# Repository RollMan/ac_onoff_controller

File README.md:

## Appearance

## Improvements
The 2nd servo motor (M2) must be connected to PB2 which is assigned as compare output mode.

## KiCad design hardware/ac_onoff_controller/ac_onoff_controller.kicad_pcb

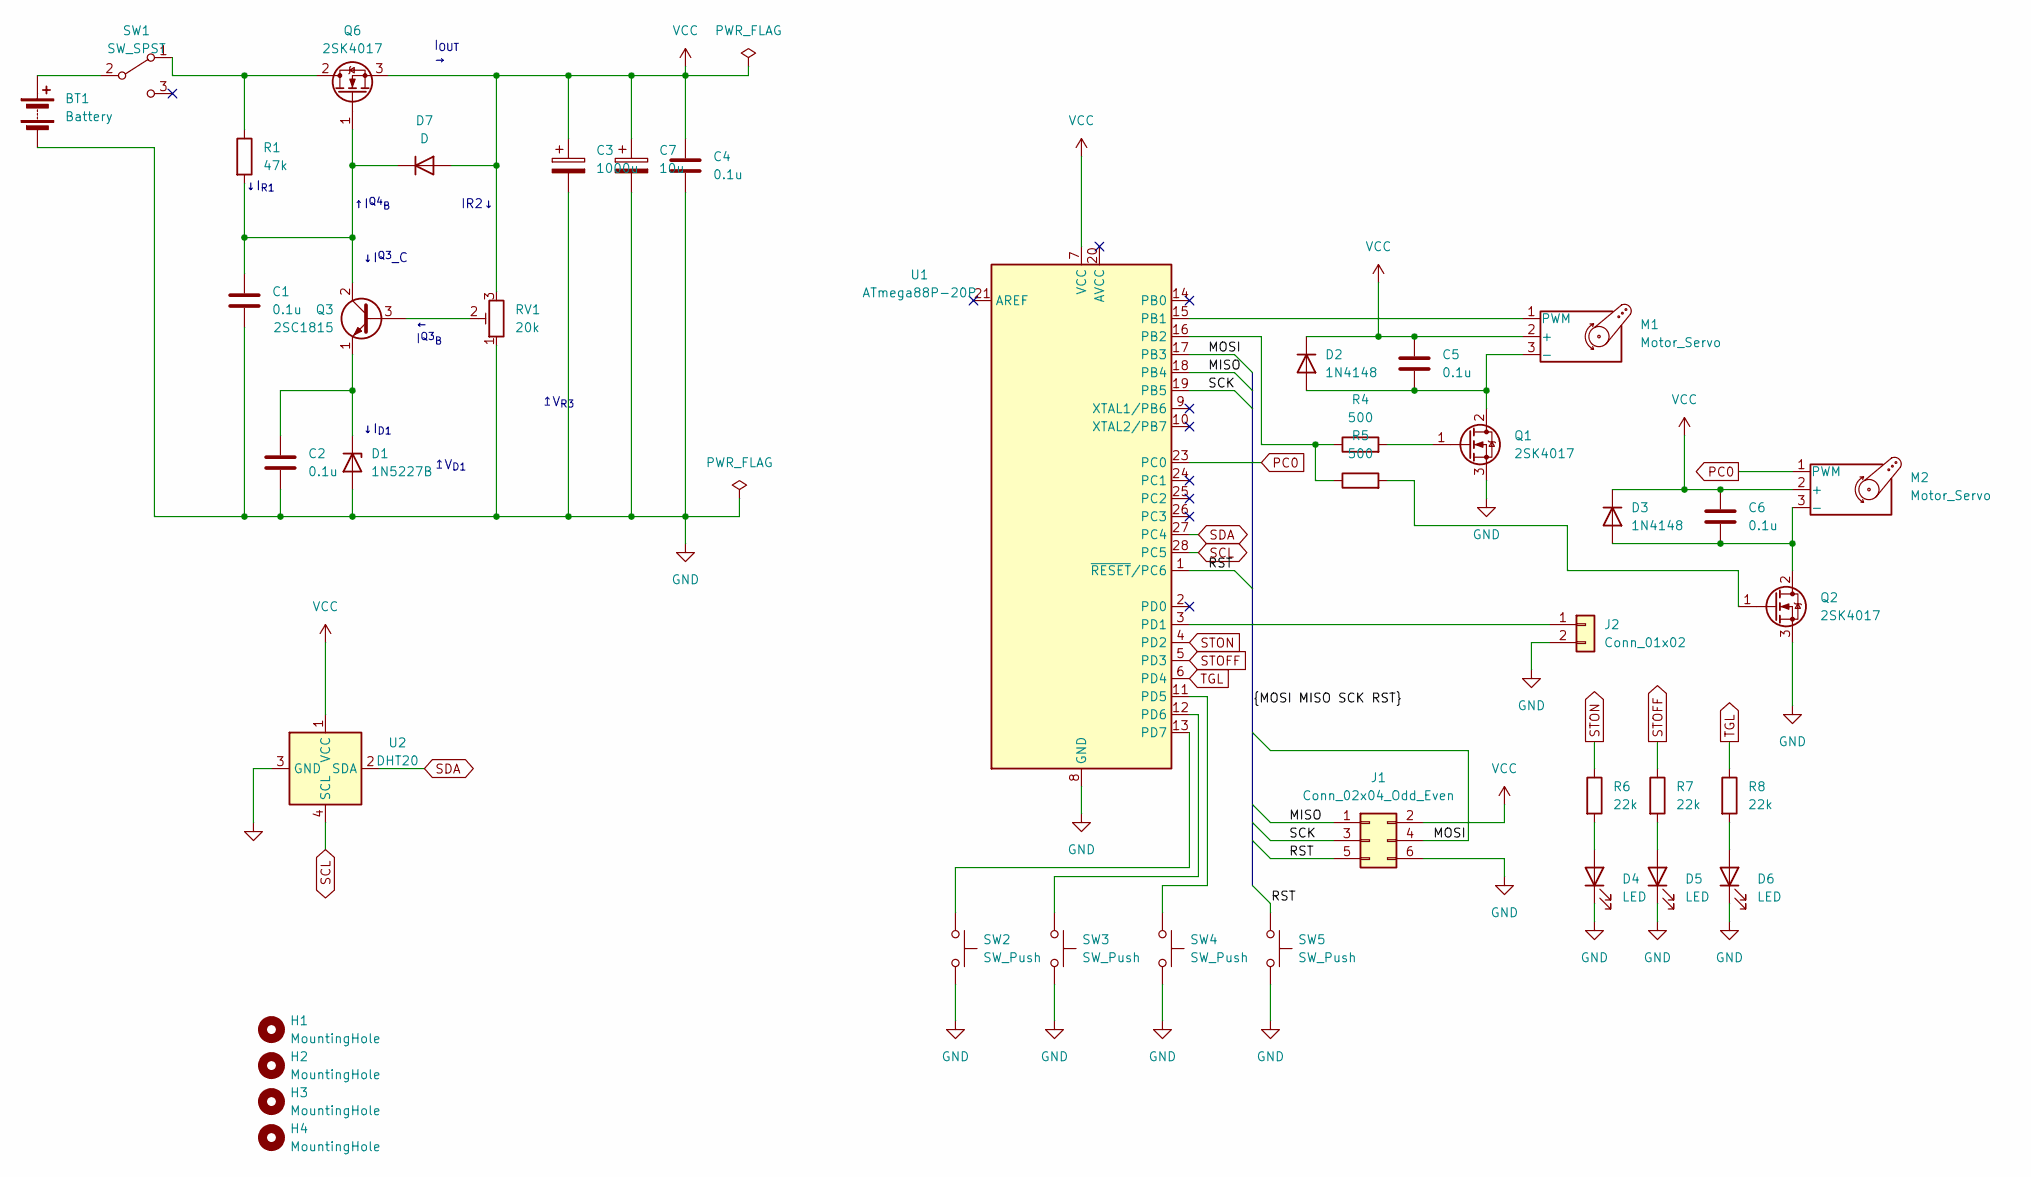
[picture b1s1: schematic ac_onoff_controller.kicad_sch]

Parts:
BT1: Battery; JST_XH_B4B-XH-A_1x04_P2.50mm_Vertical
C1, C2, C4, C5, C6: 0.1u; C_Disc_D4.3mm_W1.9mm_P5.00mm
C3: 1000u; CP_Radial_D10.0mm_P5.00mm
C7: 10u; CP_Radial_D5.0mm_P2.00mm
D1: 1N5227B; D_A-405_P10.16mm_Horizontal
D2, D3: 1N4148; D_A-405_P10.16mm_Horizontal
D4: LED; LED_D3.0mm; MPN OSDR5113A
D5: LED; LED_D3.0mm; MPN EPY5608S
D6: LED; LED_D3.0mm; MPN NOCODE(WHITE)
D7: D; D_DO-15_P12.70mm_Horizontal
H1, H2, H3, H4: MountingHole; MountingHole_3.2mm_M3
J1: Conn_02x04_Odd_Even; PinHeader_2x03_P2.54mm_Vertical
J2: Conn_01x02; PinHeader_1x02_P2.54mm_Vertical
M1, M2: Motor_Servo; PinHeader_1x03_P2.54mm_Vertical
Q1, Q2, Q6: 2SK4017; TO-251-3_Vertical; MPN 2SK4017(Q)
Q3: 2SC1815; TO-92_Inline_Wide
R1: 47k; R_Axial_DIN0309_L9.0mm_D3.2mm_P15.24mm_Horizontal
R4, R5: 500; R_Axial_DIN0309_L9.0mm_D3.2mm_P15.24mm_Horizontal
R6, R7, R8: 22k; R_Axial_DIN0309_L9.0mm_D3.2mm_P2.54mm_Vertical
RV1: 20k; GF063P
SW1: SW_SPST; SS-22F25-G4; MPN SS-22F25-G4
SW2, SW3, SW4, SW5: SW_Push; SW_PUSH_6mm_H7.3mm
U1: ATmega88P-20P; DIP-28_W7.62mm
U2: DHT20; Aosong_DHT20

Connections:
/MISO: J1.1, U1.18 (PB4)
/MOSI: J1.4, U1.17 (PB3)
/RST: J1.5, SW5.1, U1.1 (~RESET/PC6)
/SCK: J1.3, U1.19 (PB5)
GND: BT1.2 (-), C1.2, C2.2, C3.2, C4.2, C7.2, D1.2 (A), D4.1 (K), D5.1 (K), D6.1 (K), J1.6, J2.2, Q1.3 (S), Q2.3 (S), RV1.1, SW2.2, SW3.2, SW4.2, SW5.2, U1.8 (GND), U1.22 (GND), U2.3 (GND)
unnamed: BT1.1 (+), SW1.2 (B)
unnamed: C2.1, D1.1 (K), Q3.1 (E)
unnamed: C5.2, D2.2 (A), M1.3 (-), Q1.2 (D)
unnamed: C6.2, D3.2 (A), M2.3 (-), Q2.2 (D)
unnamed: D4.2 (A), R6.2
unnamed: D5.2 (A), R7.2
unnamed: D6.2 (A), R8.2
unnamed: C1.1, D7.1 (K), Q3.2 (C), Q6.1 (G), R1.2
unnamed: J2.1, U1.3 (PD1)
unnamed: M1.1 (PWM), U1.15 (PB1)
unnamed: Q1.1 (G), R4.2
unnamed: Q2.1 (G), R5.2
unnamed: Q3.3 (B), RV1.2
unnamed: Q6.2 (D), R1.1, SW1.1 (A)
unnamed: R4.1, R5.1, U1.16 (PB2)
unnamed: SW4.1, U1.11 (PD5)
unnamed: SW3.1, U1.12 (PD6)
unnamed: SW2.1, U1.13 (PD7)
PC0: M2.1 (PWM), U1.23 (PC0)
SCL: U1.28 (PC5), U2.4 (SCL)
SDA: U1.27 (PC4), U2.2 (SDA)
STOFF: R7.1, U1.5 (PD3)
STON: R6.1, U1.4 (PD2)
TGL: R8.1, U1.6 (PD4)
VCC: C3.1, C4.1, C5.1, C6.1, C7.1, D2.1 (K), D3.1 (K), D7.2 (A), J1.2, M1.2 (+), M2.2 (+), Q6.3 (S), RV1.3, U1.7 (VCC), U2.1 (VCC)

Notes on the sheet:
↑I^{Q4}_{B}
IR2↓
↓I_{D1}
↓I^{Q3}_C
I_{OUT} →
↓I_{R1}
↥V_{R3}
← I^{Q3}_{B}
↥V_{D1}

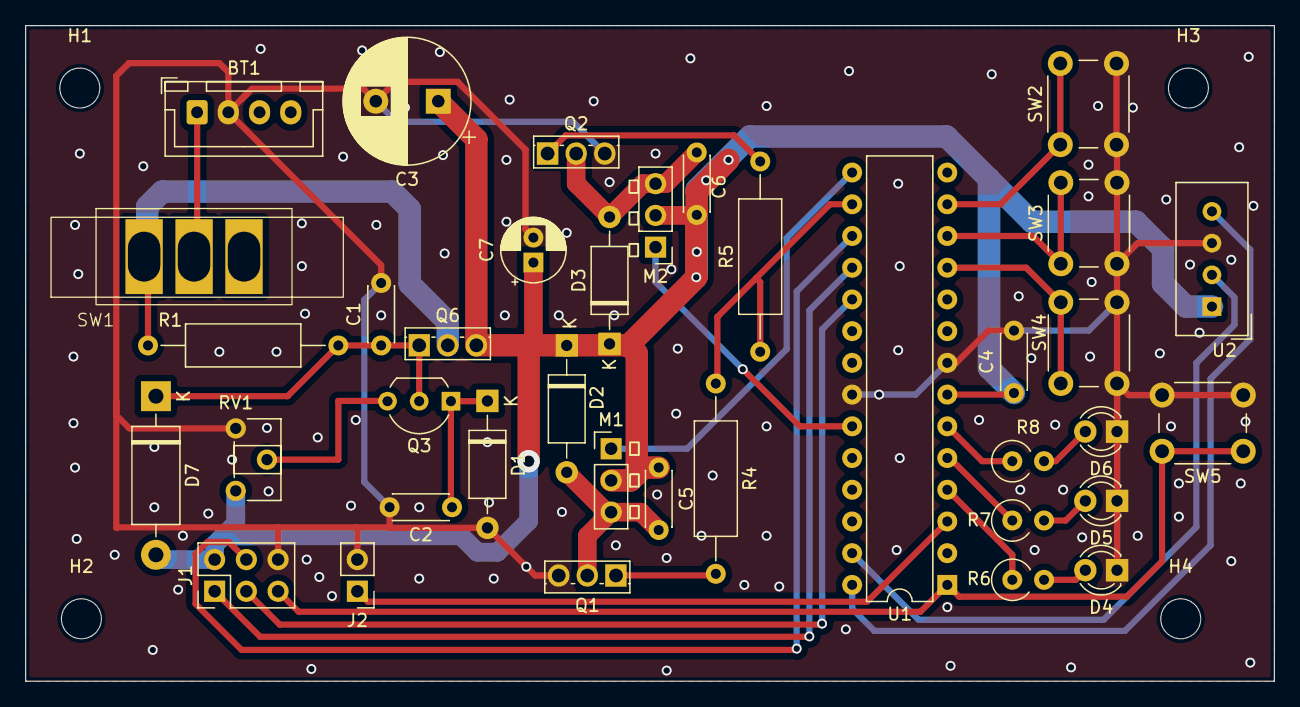
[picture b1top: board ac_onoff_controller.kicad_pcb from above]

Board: 2 copper layers, 100.0 x 52.5 mm, 41 parts (0 on the bottom side), 30 nets.

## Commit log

2024-07-23 debug
2024-07-23 fix pin assigmnents
2024-07-23 add pcb
2024-07-23 wip: modify footprints etc. for ordering PCBs
2024-07-24 modify footprints etc. for ordering PCBs
2024-07-25 wip: add a new pcb design for ordering to vendors
2024-07-27 add a new pcb design for ordering to vendors
2024-07-30 use trim register for voltage regulator feedback
2024-07-30 add mpn of a trim register
2024-07-30 add vias
2024-07-30 change via size constraints
2024-07-31 export gerbers for jlcpcb
2024-07-31 adjust silkscreen placements
2024-07-31 add the MPN of DHT20
2024-09-09 add some notes of improvement points
2024-09-11 update libraries that supports the new board
2024-09-11 update main routine to support updated libraries
2024-09-11 enable buttons on the board to current recognition of A/C power status
2024-09-11 add a board appearance to readme
2024-09-12 supress optimization for a variable used in interruptions
2024-09-12 add a release build configuration
